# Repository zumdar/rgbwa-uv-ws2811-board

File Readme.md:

# RGBWA+UV LED with 2x WS2811 chipss

fun collab w/ eddie farr!

Eddie made CamperLightsSMD and I modified and made the dome_rgbwauv_pcb file

# dome_rgbwauv_pcb

For the LED dome / barnacle project
Rev. A:
- features mosfet circuit so more current can go to the led
- jumper so you can toggle between the mosfet circuit and just using the ws2811 output
- 2x holes (H1 & H2) should line up so you can screw this pcb into the plastic dome and use it as base
- JST connector on back so you can connect data and power easily
- 4 other holes to mount standoffs so you can mount this on a substrate?
- hole in middle of LED for heatsink

# similar projects
Neopixel XL - https://github.com/palsayantan/Neopixel-XL

## REV. A renders
front:

back:

[Rev A Layout PDF](dome_rgbwauv_pcb/dome_rgbwauv_pcb_LAYOUT.pdf)
## Schematic 
[Schematic](dome_rgbwauv_pcb/dome_rgbwauv_Schematic.pdf)

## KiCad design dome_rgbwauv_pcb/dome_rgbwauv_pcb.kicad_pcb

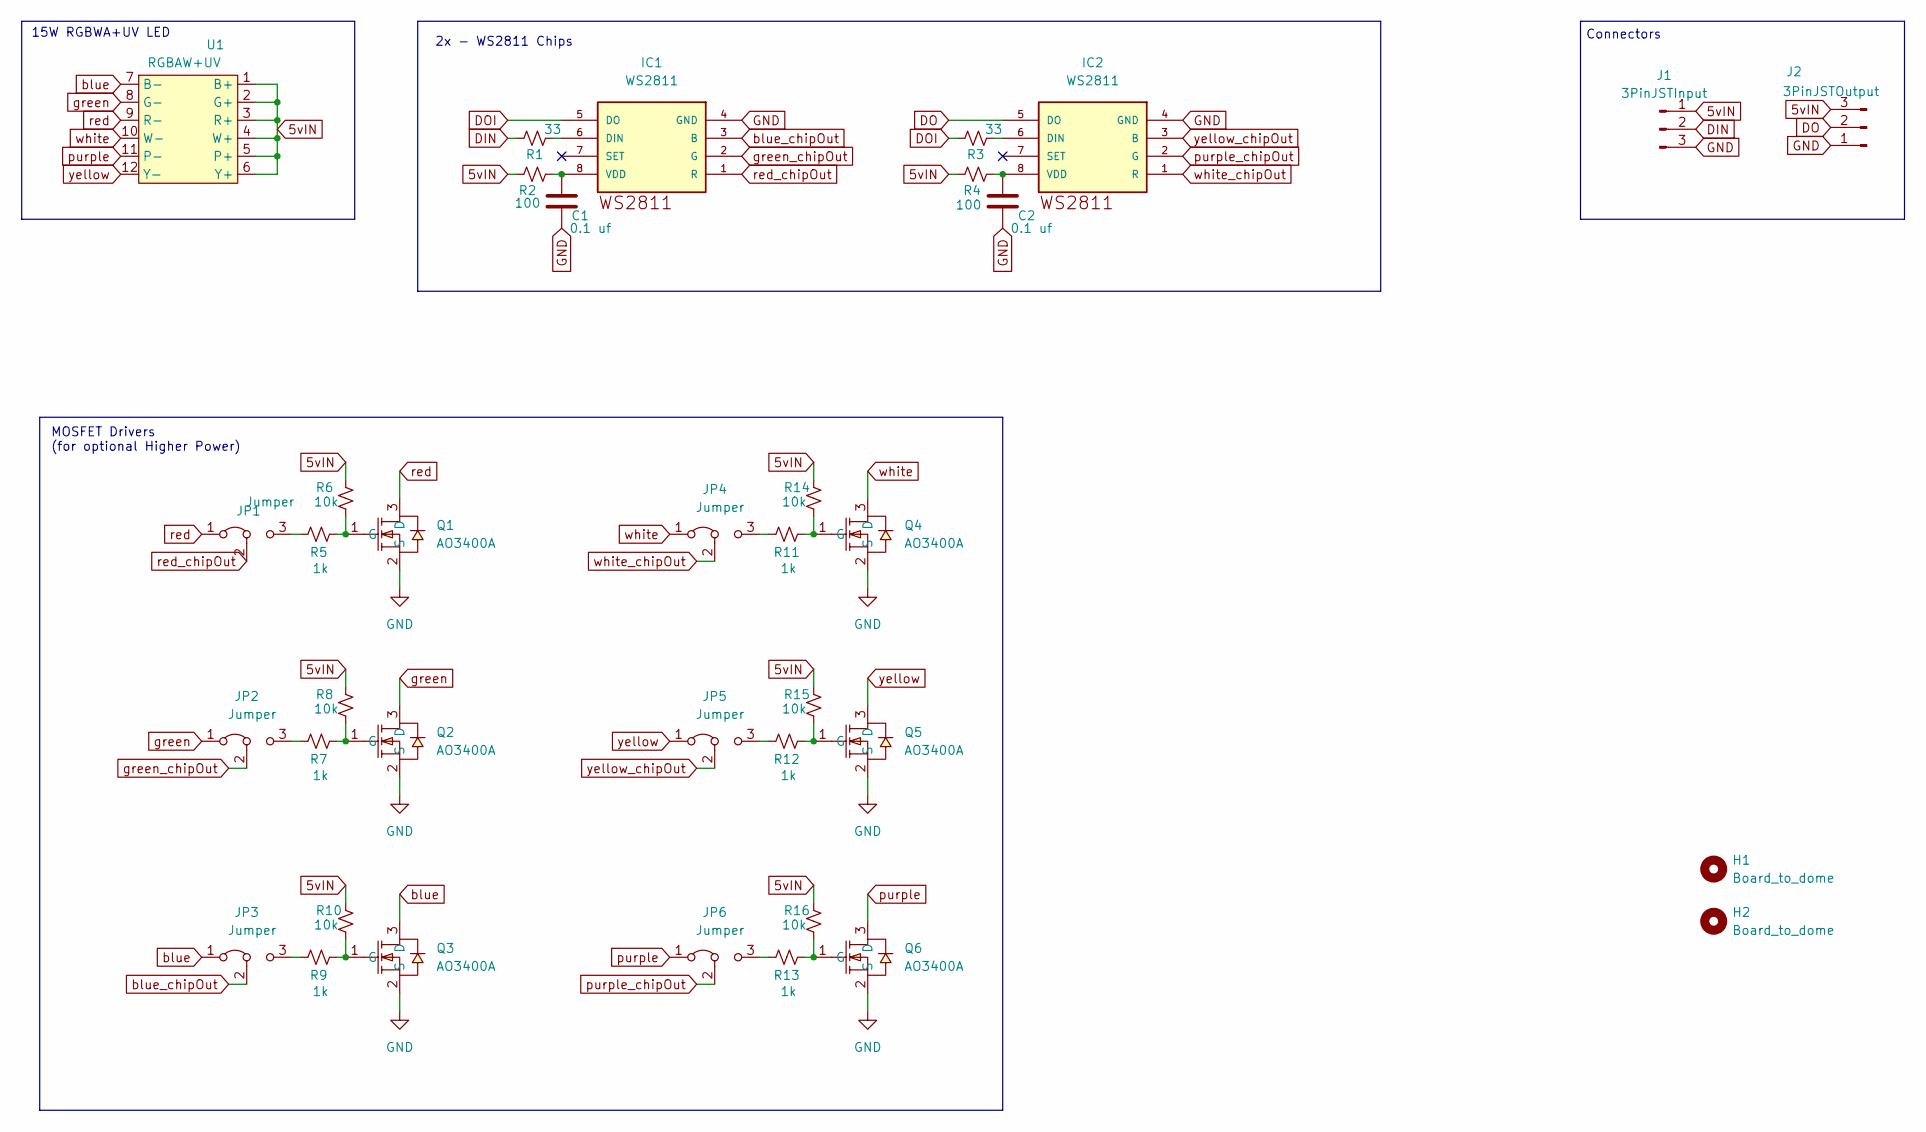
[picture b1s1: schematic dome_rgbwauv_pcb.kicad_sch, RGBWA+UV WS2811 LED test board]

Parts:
C1, C2: 0.1 uf; C_0603_1608Metric
H1, H2: Board_to_dome; MountingHole_2.2mm_M2
IC1, IC2: WS2811; SO08-SKINNYPADS
J1: 3PinJSTInput; JST_EH_B3B-EH-A_1x03_P2.50mm_Vertical
J2: 3PinJSTOutput; JST_EH_B3B-EH-A_1x03_P2.50mm_Vertical
JP1, JP2, JP3, JP4, JP5, JP6: Jumper; PinHeader_1x03_P2.54mm_Vertical
Q1, Q2, Q3, Q4, Q5, Q6: AO3400A; SOT-23-3_L2.9-W1.6-P1.90-LS2.8-BR; LCSC Part C20917
R1, R3: 33; R_0603_1608Metric
R2, R4: 100; R_0603_1608Metric
R5, R7, R9, R11, R12, R13: 1k; R_0603_1608Metric
R6, R8, R10, R14, R15, R16: 10k; R_0603_1608Metric
U1: RGBAW+UV; RGBWA+UV

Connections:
5vIN: J1.1, J2.3, R2.1, R4.1, R6.1, R8.1, R10.1, R14.1, R15.1, R16.1, U1.1 (B+), U1.2 (G+), U1.3 (R+), U1.4 (W+), U1.5 (P+), U1.6 (Y+)
DIN: J1.2, R1.1
DO: IC2.5 (DO), J2.2
DOI: IC1.5 (DO), R3.1
GND: C1.2, C2.2, IC1.4 (GND), IC2.4 (GND), J1.3, J2.1, Q1.2 (S), Q2.2 (S), Q3.2 (S), Q4.2 (S), Q5.2 (S), Q6.2 (S)
unnamed: IC1.6 (DIN), R1.2
unnamed: C1.1, IC1.8 (VDD), R2.2
unnamed: IC2.6 (DIN), R3.2
unnamed: C2.1, IC2.8 (VDD), R4.2
unnamed: JP1.3 (B), R5.1
unnamed: JP2.3 (B), R7.1
unnamed: JP3.3 (B), R9.1
unnamed: JP4.3 (B), R11.1
unnamed: JP5.3 (B), R12.1
unnamed: JP6.3 (B), R13.1
unnamed: Q1.1 (G), R5.2, R6.2
unnamed: Q2.1 (G), R7.2, R8.2
unnamed: Q3.1 (G), R9.2, R10.2
unnamed: Q4.1 (G), R11.2, R14.2
unnamed: Q5.1 (G), R12.2, R15.2
unnamed: Q6.1 (G), R13.2, R16.2
blue: JP3.1 (A), Q3.3 (D), U1.7 (B-)
blue_chipOut: IC1.3 (B), JP3.2 (C)
green: JP2.1 (A), Q2.3 (D), U1.8 (G-)
green_chipOut: IC1.2 (G), JP2.2 (C)
purple: JP6.1 (A), Q6.3 (D), U1.11 (P-)
purple_chipOut: IC2.2 (G), JP6.2 (C)
red: JP1.1 (A), Q1.3 (D), U1.9 (R-)
red_chipOut: IC1.1 (R), JP1.2 (C)
white: JP4.1 (A), Q4.3 (D), U1.10 (W-)
white_chipOut: IC2.1 (R), JP4.2 (C)
yellow: JP5.1 (A), Q5.3 (D), U1.12 (Y-)
yellow_chipOut: IC2.3 (B), JP5.2 (C)

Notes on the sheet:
15W RGBWA+UV LED
Connectors
MOSFET Drivers (for optional Higher Power)
2x - WS2811 Chips

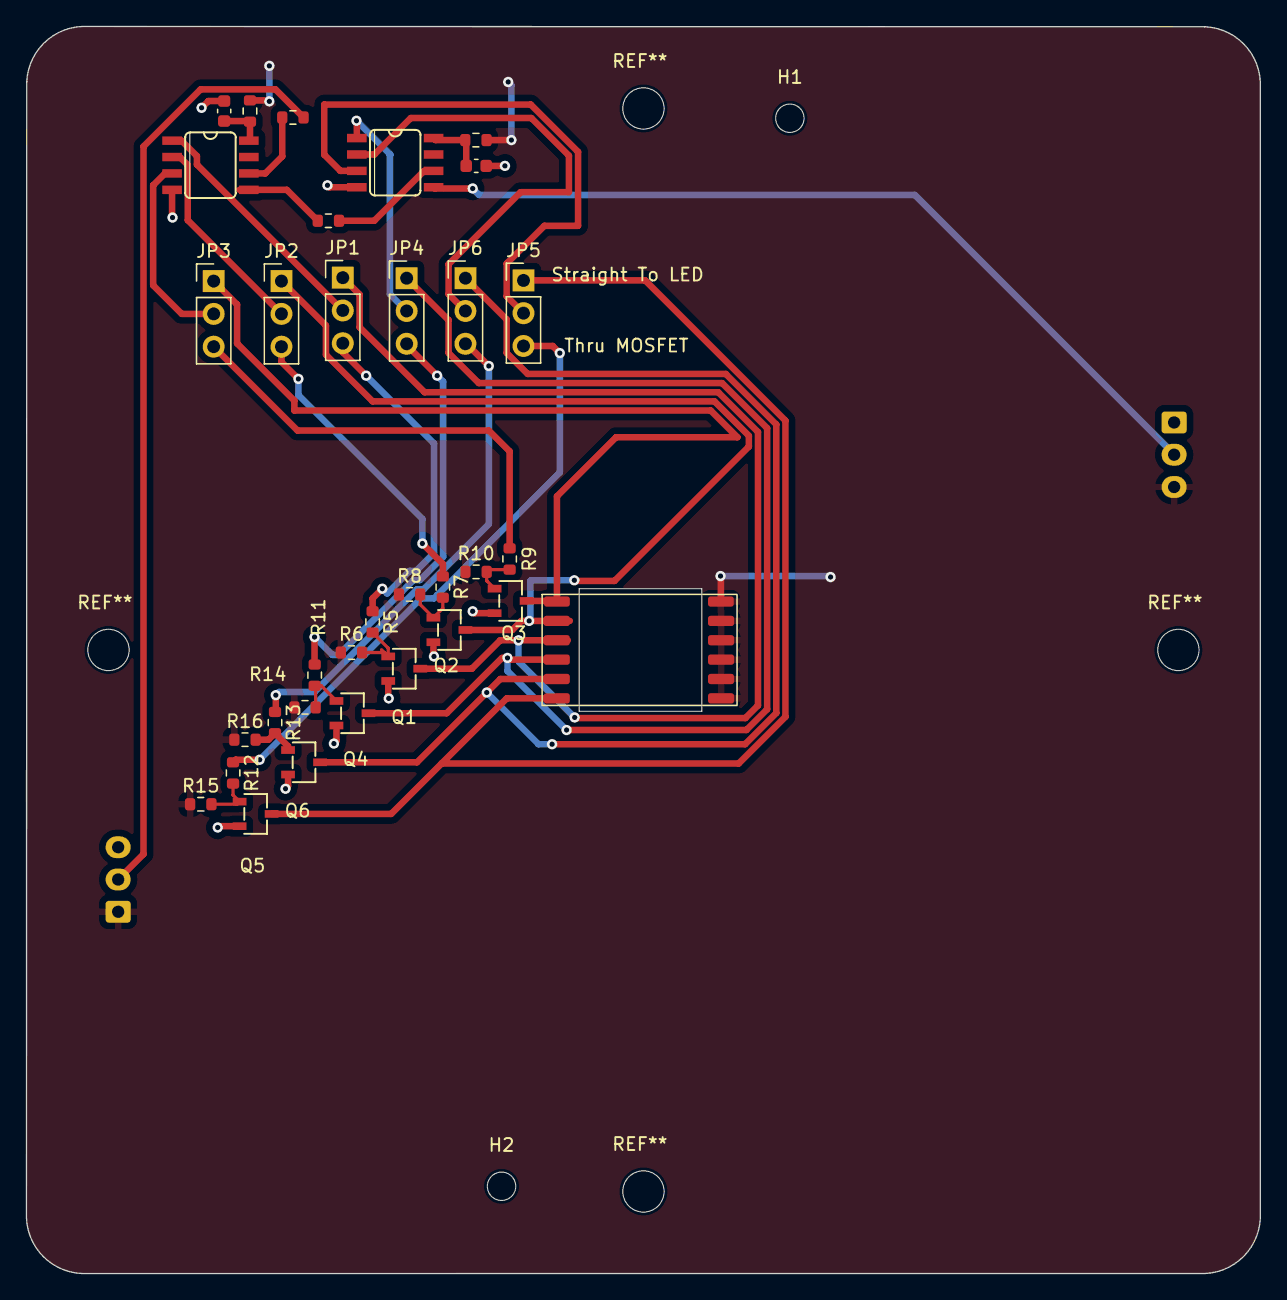
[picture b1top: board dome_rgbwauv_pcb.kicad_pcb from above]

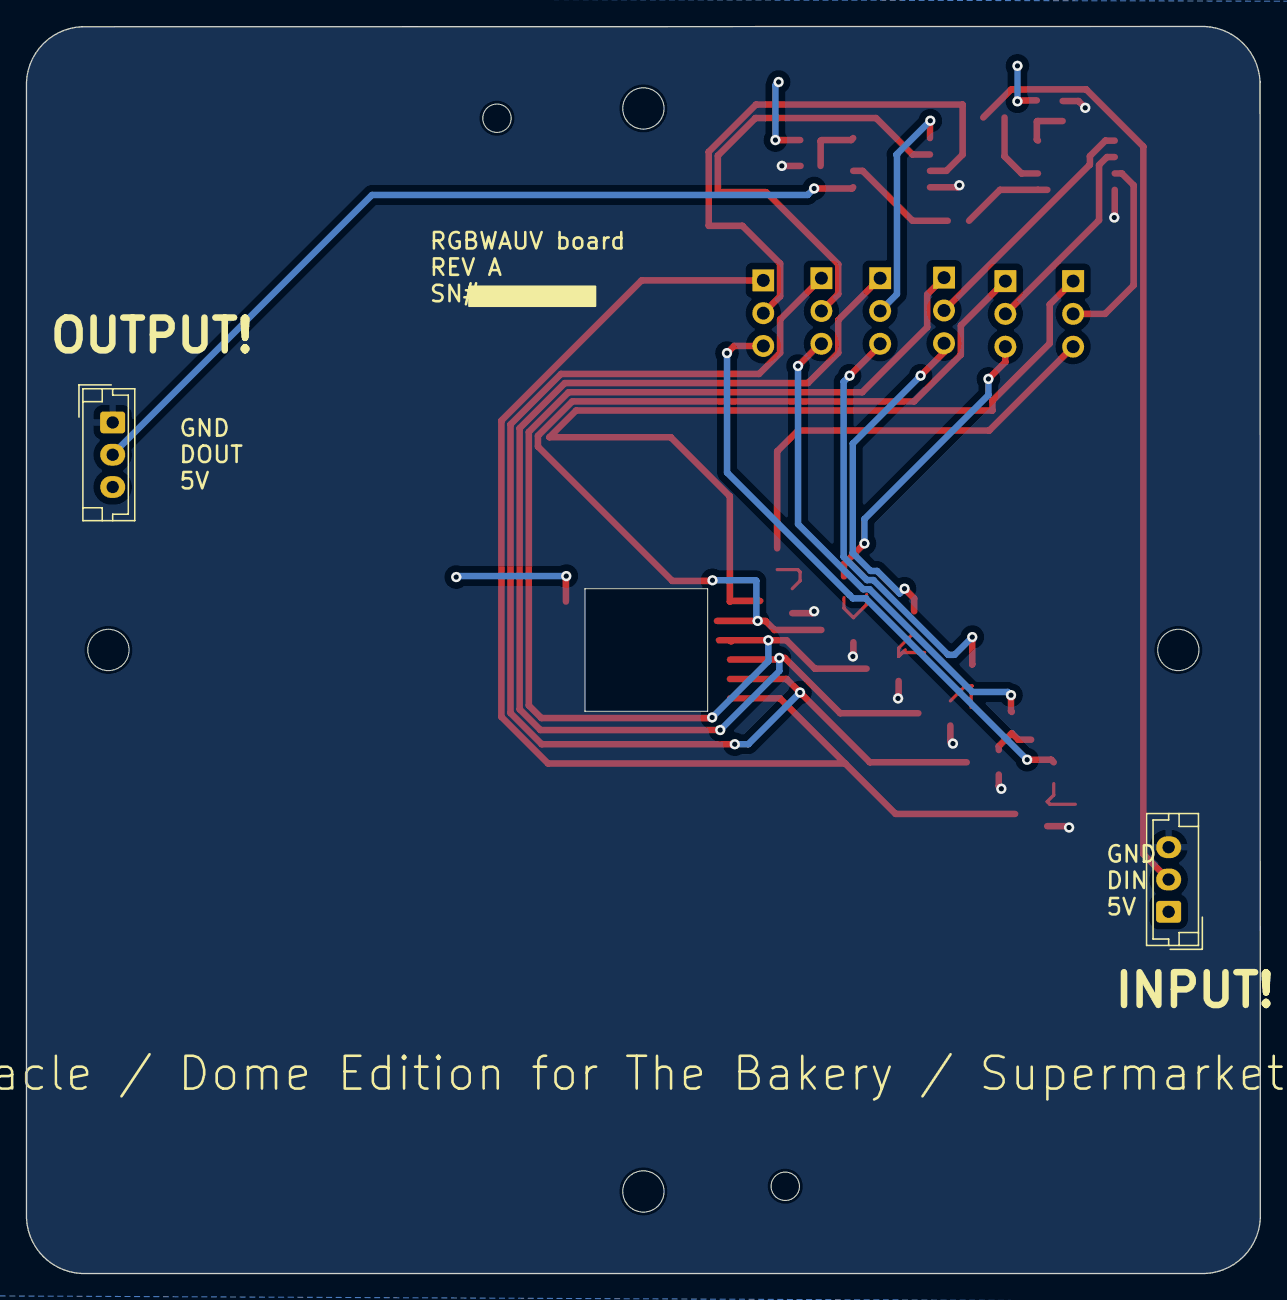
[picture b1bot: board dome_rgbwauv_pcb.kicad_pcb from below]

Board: 2 copper layers, 95.6 x 96.6 mm, 37 parts (2 on the bottom side), 33 nets.

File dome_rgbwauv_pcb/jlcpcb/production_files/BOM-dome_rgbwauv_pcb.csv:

Comment,Designator,Footprint,LCSC
0.1 uf,"C1,C2",C_0603_1608Metric,C14663
AO3400A,"Q1,Q2,Q3,Q4,Q5,Q6",SOT-23-3_L2.9-W1.6-P1.90-LS2.8-BR,C20917
1k,"R11,R12,R13,R5,R7,R9",R_0603_1608Metric,C21190
100,"R2,R4",R_0603_1608Metric,C22775
33,"R1,R3",R_0603_1608Metric,C23140
10k,"R10,R14,R15,R16,R6,R8",R_0603_1608Metric,C25804
WS2811,"IC1,IC2",SO08-SKINNYPADS,C2920043
RGBAW+UV,U1,RGBWA+UV,
Board_to_dome,H2,MountingHole_2.2mm_M2,
Board_to_dome,H1,MountingHole_2.2mm_M2,
3PinJSTOutput,J2,JST_EH_B3B-EH-A_1x03_P2.50mm_Vertical,
3PinJSTInput,J1,JST_EH_B3B-EH-A_1x03_P2.50mm_Vertical,
Jumper,JP1,PinHeader_1x03_P2.54mm_Vertical,
Jumper,JP2,PinHeader_1x03_P2.54mm_Vertical,
Jumper,JP5,PinHeader_1x03_P2.54mm_Vertical,
Jumper,JP3,PinHeader_1x03_P2.54mm_Vertical,
Jumper,JP4,PinHeader_1x03_P2.54mm_Vertical,
Jumper,JP6,PinHeader_1x03_P2.54mm_Vertical,

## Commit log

2024-03-31 init;
2024-03-31 adding readme and nicer pdf
2024-03-31 readme
2024-04-04 Add files via upload
    adding led data sheet eddie emailed me
